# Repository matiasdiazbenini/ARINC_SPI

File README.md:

# ARINC_SPI

Repositorio de trabajo del proyecto PAMPA orientado a la recreacion logica/temporal de un enlace tipo ARINC 429 usando:

- 3 Raspberry Pi Pico / Pico 2 W
- 1 Raspberry Pi 3B+
- dashboard Flask
- bridge HTTP/SPI
- Prometheus + Grafana

Este repositorio estuvo originalmente centrado en el firmware del transmisor, pero fue ampliado y reorganizado para conservar en un solo lugar el estado real de la fase `arinc429_logic`, su documentacion y la evidencia de laboratorio.

## Estado actual

La fase validada hasta el momento es:

- `arinc429_logic`

Quedo validado:

- enlace `master -> slave` en `100 kbps` y `12.5 kbps`
- ACK reverso `slave -> master`
- captura pasiva con `ARINC-SNIFFER`
- exportacion por SPI hacia la Raspberry Pi 3B+
- bridge HTTP
- dashboard Flask
- Prometheus + Grafana
- corrida post tutor con `spi_errors = 0` en regimen estable
- separacion de errores SPI de arranque (`spi_startup_errors`) y operativos (`spi_errors`)
- transporte SPI por tramas completas validado con `sniffer_arinc429_logic_pio_frame`
- corrida PIO-frame de 6-7 horas con `spi_errors = 0`
- mecanismo DRDY implementado para consultar snapshot por demanda
- recuperacion V5 implementada para:
  - resincronizar captura ARINC esperando reposo electrico del canal
  - resetear transporte SPI `pio-frame` con trama completa de `32 bytes`
  - supervisar bridge/Flask con modo dios v2 (`arinc-supervisor.service`)
  - clasificar estados y ejecutar recuperacion escalonada
- paridad estricta implementada en RX y SNIFFER
- deteccion autonoma en sniffer de velocidad `FWD` entre `100 kbps` y `12.5 kbps`
- resync FWD separados entre arranque y regimen
- exportacion de pruebas a CSV, JSON y PDF desde la 3B+
- prueba de paridad estricta validada con balance exacto de contadores
- corridas finales de `8 horas` a `100 kbps` y `12.5 kbps`, ambas con cero
  errores operativos, cero errores de paridad, cero overflow y cero drops SPI
- validacion con osciloscopio de:
  - retorno a cero
  - pulsos de `5 us`
  - bit time de `10 us`
  - modo autorate:
    - `100 kbps`: palabra de `320 us` y gap visible de `44 us`
    - `12.5 kbps`: media celda de `40 us`, bit de `80 us` y gap visible de
      `360 us`
    - relacion de gaps `360/44 = 8.18`, coherente con la relacion teorica `8:1`
  - reconstruccion diferencial `+3.3 / 0 / -3.3 V`

## Estructura del repo

- [ARINC-TX](ARINC-TX/README.md)
  - firmware del nodo transmisor
- [ARINC-RX](ARINC-RX/README.md)
  - snapshot del firmware del nodo receptor usado en esta etapa
- [ARINC-SNIFFER](ARINC-SNIFFER/README.md)
  - snapshot del firmware sniffer y protocolo SPI asociado
- [HOST_3b+](HOST_3b+/README.md)
  - bridge SPI/HTTP, diagnosticos y scripts de host
- [DASHBOARD_WEB/arinc_dashboard](DASHBOARD_WEB/arinc_dashboard/README.md)
  - dashboard web operativo
- [prometheus](prometheus/README.md)
  - configuracion de Prometheus usada en la notebook
- [ELECTRICO](ELECTRICO/frontend_arinc429_lab/README.md)
  - front-end electrico de laboratorio, esquematico/PCB KiCad y relevamiento de componentes
- [imagenes](imagenes/)
  - capturas de osciloscopio organizadas por enlace y canal
- [docs](docs/README.md)
  - indice de documentacion y memoria externa del proyecto
- [tools](tools/)
  - scripts WSL para deploy, healthcheck y control de servicios en la 3B+
- [PROJECT_CONTEXT.md](PROJECT_CONTEXT.md)
  - archivo maestro de handoff para retomar rapido el trabajo
- raiz del repo:
  - README, contexto maestro y estado de fase
- `docs/`:
  - documentacion general
  - PDFs generados
  - fuentes Overleaf/LaTeX
  - scripts generadores
- `ELECTRICO/`:
  - proyecto KiCad inicial para el acondicionamiento electrico ARINC-like
  - PCB preliminar de laboratorio
  - relevamiento de componentes con precios, alternativas y correspondencia con el esquematico

## Topologia actual recomendada

- Pico transmisor:
  - genera `FWD_A` por `GP6` y `FWD_B` por `GP7`
- Pico receptor:
  - recibe `FWD`
  - responde `ACK` por `GP4/GP5`
- Pico sniffer:
  - escucha `FWD` y `REV`
  - no transmite sobre lineas ARINC
  - filtra por `label + SDI`
  - exporta snapshot/eventos por SPI
- Raspberry Pi 3B+:
  - consume SPI del sniffer
  - publica bridge HTTP local en `127.0.0.1:5100`
  - corre Flask hacia la red en `:5000`
- Notebook:
  - accede al dashboard
  - scrapea metricas desde Flask
  - corre Prometheus en `:9090`
  - corre Grafana en `:3000`

## Red recomendada

La configuracion que mejor resultado dio para estabilidad larga fue:

- notebook por Wi-Fi a Internet, si hace falta
- notebook por Ethernet directo a la Raspberry Pi 3B+
- IP fija de la notebook en Ethernet:
  - `192.168.50.1/24`
- IP fija de la Raspberry Pi 3B+ en Ethernet:
  - `192.168.50.2/24`

Se observo que esta configuracion es mas robusta que dejar la 3B+ colgada por Wi-Fi para el trafico operativo del sistema.

Acceso recomendado desde la notebook:

- dashboard Flask:
  - `http://192.168.50.2:5000`
- metricas para Prometheus:
  - `http://192.168.50.2:5000/metrics`

El bridge SPI/HTTP queda local dentro de la 3B+ en `http://127.0.0.1:5100`; Flask lo consulta por loopback.

## Modo stream post tutor

Ademas del modo laboratorio batch/ACK, quedo validada la transmision sin depender de bloques fijos de `1000` palabras:

- TX:
  - `arinc_tx_arinc429_logic_stream`
- RX:
  - `arinc_rx_arinc429_logic_stream`
- Sniffer:
  - `sniffer_arinc429_logic_pio_frame`

En este ensayo, `ARINC-TX` transmite rafagas de longitud variable y no espera ACK. `ARINC-RX` procesa palabras a medida que llegan y no emite ACK por `REV`. Por eso, en el dashboard, `TEMPERATURA`, `VELOCIDAD` y `ALTITUD` deben crecer; `ACK_BATCH` puede quedar ausente o congelado.

Criterios de prueba:

- `spi_errors = 0`
- `spi_drop_events = 0`
- `overflow_events = 0`
- `parity_errors_sniffer = 0`

Resultado de aproximadamente `10 horas`:

- `accepted_words = 22,756,775`
- `ack_events = 0`
- `spi_errors = 0`
- `spi_startup_errors = 6`
- `spi_drop_events = 0`
- `overflow_events = 0`
- `parity_errors_sniffer = 0`
- `fwd_resync_events = 3`

Evidencia:

- [evidencia_stream_aleatorio_post_tutor.md](docs/evidencia_stream_aleatorio_post_tutor.md)

## Modo autorate 100 kbps / 12.5 kbps

Para probar la capacidad de `ARINC-SNIFFER` de detectar la velocidad sin que TX
ni RX se la informen por configuracion externa, se agrego el target:

- TX:
  - `arinc_tx_arinc429_logic_stream_autorate`
  - `arinc_tx_arinc429_logic_stream_12k5` para forzar la velocidad baja en una
    prueba controlada

Este firmware elige al arrancar entre `100 kbps` y `12.5 kbps`. El RX stream
no requiere cambio porque su PIO recibe por flancos/nivel activo. El sniffer
publica la velocidad detectada como `detected_bit_rate_bps` y
`detected_bit_rate_txt` en `/stats`, y como `arinc_detected_bit_rate_bps` en
Prometheus.

Validacion observada:

- el TX arranco en distintas corridas tanto a `100 kbps` como a `12.5 kbps`
- corrida de `30 min` a `12.5 kbps`:
  - `detected_bit_rate_bps = 12500`
  - `received_words = 618,842`
  - `accepted_words = 185,652`
  - `spi_errors = 0`
- corrida de `30 min` a `100 kbps`:
  - `detected_bit_rate_bps = 100000`
  - `received_words = 4,807,727`
  - `accepted_words = 1,442,318`
  - `spi_errors = 0`
- ambas corridas cerraron con:
  - `parity_errors_sniffer = 0`
  - `overflow_events = 0`
  - `spi_drop_events = 0`
  - balance de clasificacion igual a `0`
- corridas finales de `8 horas`:
  - `12.5 kbps`: `received_words = 9,876,638`,
    `accepted_words = 2,962,992`, `spi_errors = 0`
  - `100 kbps`: `received_words = 76,707,606`,
    `accepted_words = 23,012,283`, `spi_errors = 0`
  - ambas con `parity_errors_sniffer = 0`, `overflow_events = 0`,
    `spi_drop_events = 0`, `fwd_operational_resync_events = 0` y
    `supervisor_health = ok`

Evidencia:

- [evidencia_autorate_100k_12k5.md](docs/evidencia_autorate_100k_12k5.md)
- [evidencia_corridas_finales_autorate_8h.md](docs/evidencia_corridas_finales_autorate_8h.md)

## Forma recomendada de trabajo

Hay dos maneras comodas de trabajar:

- abrir la raiz del repo para tener toda la arquitectura visible
- abrir una subcarpeta puntual cuando quieras concentrarte en un componente

Por ejemplo:

- `ARINC-TX/`
- `ARINC-RX/`
- `ARINC-SNIFFER/`
- `HOST_3b+/`
- `DASHBOARD_WEB/arinc_dashboard/`

Tambien se pueden abrir varias ventanas de VS Code en paralelo, una por componente, sin problema.

## Operacion Raspberry 3B+ desde WSL

Ademas de WinSCP, el repo incluye scripts para actualizar y verificar la 3B+
por SSH/rsync desde WSL:

- [Operacion Raspberry Pi 3B+ con scripts](docs/operacion_raspberry_3b_deploy.md)

Comandos principales:

```bash
./tools/raspi_deploy.sh
./tools/raspi_healthcheck.sh
./tools/raspi_services.sh status
```

## Perfil operativo recomendado

Para el bridge/dashboard, el perfil que mejor balance dio entre fluidez y estabilidad fue:

- modo PIO-frame validado post tutor:
  - `ARINC_SPI_TRANSFER_MODE = pio-frame`
  - `ARINC_SPI_MANUAL_CS = 1`
  - `ARINC_SPI_CS_SETUP_US = 100`
  - `ARINC_SPI_CS_HOLD_US = 100`
  - `ARINC_SPI_HZ = 8000000`
  - `ARINC_SPI_BYTE_DELAY_US = 0`
  - corrida de aproximadamente `9 horas` con `spi_errors = 0`
- fallback PIO-frame conservador:
  - `ARINC_SPI_HZ = 400000`
- modo byte validado como fallback estable:
  - `ARINC_SPI_TRANSFER_MODE = byte`
  - `ARINC_SPI_HZ = 800000`
  - `ARINC_SPI_BYTE_DELAY_US = 25`

Perfil historico estable previo al PIO-frame:

- `ARINC_SPI_HZ = 800000`
- `ARINC_SPI_TRANSFER_MODE = byte`
- `ARINC_SPI_BYTE_DELAY_US = 25`
- `ARINC_SPI_POLL_SEC = 0.006`
- `ARINC_SPI_STATS_SEC = 0.06`
- `ARINC_SPI_RESPONSE_DELAY_SEC = 0.00005`
- refresh Flask:
  - `33 ms`

El perfil de estres mas agresivo fue probado y aguanto varias horas, pero con una tasa de `spi_errors` mucho mayor, por lo que no se deja como modo continuo recomendado.

## Documentos clave

- [Entrega consolidada para el tutor](docs/entrega_tutor/README.md)
- [Trabajo final en formato tesis PDF](docs/pdf/trabajo_final_arinc429.pdf)
- [Fuente LaTeX del trabajo final](docs/tex/trabajo_final_arinc429.tex)
- [PROJECT_CONTEXT.md](PROJECT_CONTEXT.md)
- [FASE2_ARINC429_LOGIC.md](FASE2_ARINC429_LOGIC.md)
- [resumen_proyecto_arinc429.md](docs/resumen_proyecto_arinc429.md)
- [instructivo_osciloscopio_arinc429_logic.md](docs/instructivo_osciloscopio_arinc429_logic.md)
- [evidencia_spi_errors_cero_post_tutor.md](docs/evidencia_spi_errors_cero_post_tutor.md)
- [evidencia_spi_pio_frame_post_tutor.md](docs/evidencia_spi_pio_frame_post_tutor.md)
- [procedimiento_prueba_paridad_estricta.md](docs/procedimiento_prueba_paridad_estricta.md)
- [procedimiento_registro_estadistico.md](docs/procedimiento_registro_estadistico.md)
- [evidencia_corrida_final_stream_8mhz_8h.md](docs/evidencia_corrida_final_stream_8mhz_8h.md)
- [evidencia_corridas_finales_autorate_8h.md](docs/evidencia_corridas_finales_autorate_8h.md)
- [evidencia_osciloscopio_autorate_20260629.md](docs/evidencia_osciloscopio_autorate_20260629.md)
- [tesis_fuente_overleaf_arinc429.tex](docs/tex/tesis_fuente_overleaf_arinc429.tex)
- [trabajo_final_arinc429.tex](docs/tex/trabajo_final_arinc429.tex)
- [modelo_osi_arquitectura_arinc429.tex](docs/tex/modelo_osi_arquitectura_arinc429.tex)
- [osciloscopio_descripcion_imagenes.tex](docs/tex/osciloscopio_descripcion_imagenes.tex)

## Nota sobre ramas

Por pedido explicito del usuario, no deben tocarse las ramas:

- `MIL-M`
- `MIL-E`
- `FLASK-MIL`
- `version_estable`

correspondientes a trabajo ajeno al desarrollo ARINC actual.

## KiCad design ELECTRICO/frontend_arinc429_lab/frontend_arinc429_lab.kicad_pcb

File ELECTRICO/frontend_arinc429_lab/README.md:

# Front-end electrico ARINC 429 - banco

Proyecto KiCad inicial para revisar el acondicionamiento electrico de laboratorio.

## Estado vigente

La configuracion de banco vigente usa TL062 y fue validada el 20 de agosto de
2026 a `12,5 kbps` y `100 kbps`. El TX recibe `FWD_A` por `GP6` y `FWD_B` por
`GP7`. El detalle se encuentra en
[avance_frontend_electrico_20260820.md](../../docs/avance_frontend_electrico_20260820.md)
y las capturas originales en [evidencia/20-08](evidencia/20-08/README.md).

## Archivos

- `frontend_arinc429_lab.kicad_pro`: proyecto KiCad.
- `frontend_arinc429_lab.kicad_sch`: esquematico funcional.
- `frontend_arinc429_lab.kicad_pcb`: PCB preliminar de laboratorio.
- `exports/frontend_arinc429_lab.svg`: export del esquematico.
- `exports/frontend_arinc429_lab_pcb.svg`: vista rapida de distribucion PCB.
- `relevamiento_componentes_frontend_electrico.md`: componentes, precios, equivalencias y busqueda de disponibilidad.
- `frontend_arinc429_tl082_rework.md`: revision nueva usando TL082CP como base de TX/RX analogico.
- `exports/frontend_arinc429_tl082_rework.svg`: esquematico funcional de la revision TL082CP.
- `frontend_arinc429_tl082_circuit.kicad_pro`: proyecto KiCad del circuito TL082CP completo.
- `frontend_arinc429_tl082_circuit.kicad_sch`: esquematico de circuito con resistencias, capacitores, conectores, TL082CP y adaptacion logica.
- `exports/frontend_arinc429_tl082_circuit.svg`: export del esquematico de circuito.
- `exports/frontend_arinc429_tl082_circuit.pdf`: export PDF del esquematico de circuito.
- `memoria_calculo_frontend_tl082.tex`: memoria de calculo editable en LaTeX.
- `exports/memoria_calculo_frontend_tl082.pdf`: memoria de calculo compilada.
- `proteus/frontend_arinc429_proteus.pdsprj`: simulacion Proteus 8.15 del
  front-end TX/RX con TL082 y comparadores LM393.
- `evidencia/20260814_banco_tl082/README.md`: resultado y capturas de la
  validacion fisica del prototipo a `12,5 kbps` y `100 kbps`.
- `evidencia/20-08/README.md`: validacion vigente con TL062 a `12,5 kbps` y
  `100 kbps`.

## Alcance

Este esquema y la PCB son una base de revision y prototipo. No son todavia una
PCB final ni un transceptor certificable para campo.

## Conexion funcional

- `GP6`: TX_A_LOGIC / FWD_A.
- `GP7`: TX_B_LOGIC / FWD_B.
- `GP4`: RX_A_LOGIC.
- `GP5`: RX_B_LOGIC.
- `LINE_A/LINE_B`: par diferencial de banco.
- `+6V/-6V`: alimentacion del driver bipolar.
- `+3V3`: logica Pico y salidas de comparadores.
- `GND`: referencia comun del banco.

## Conexiones explicitas del esquematico

| Net | Desde | Hasta | Funcion |
| --- | --- | --- | --- |
| `TX_A_LOGIC` | Pico `GP6` | entrada `U1A` | dato logico lado A antes de acondicionar |
| `TX_B_LOGIC` | Pico `GP7` | entrada `U1A` | dato logico lado B antes de acondicionar |
| `LINE_A` | salida `U1A` | `J2 pin 1` y entrada `A_SENSE` | conductor A bipolar |
| `LINE_B` | salida `U1B` | `J2 pin 2` y entrada `B_SENSE` | conductor B bipolar |
| `GND_REF` | `J2 pin 3` | `GND_COMUN` | referencia de banco para medicion |
| `A_SENSE` | divisor/proteccion de `LINE_A` | entrada de `U2A` | senal reducida para comparar |
| `B_SENSE` | divisor/proteccion de `LINE_B` | entrada de `U2B` | senal reducida para comparar |
| `VTH_COMP` | divisor `R11/R12` | entradas de referencia de `U2A/U2B` | umbral de decision RX |
| `RX_A_LOGIC` | salida `U2A` | Pico `GP4` | senal recuperada A, ya en 0..3,3 V |
| `RX_B_LOGIC` | salida `U2B` | Pico `GP5` | senal recuperada B, ya en 0..3,3 V |
| `+3V3_LOGIC` | Pico/fuente 3,3 V | U2, pull-ups, divisor de umbral | alimentacion logica |
| `+6V_TX` | fuente bipolar | `U1 V+` | alimentacion positiva del TX analogico |
| `-6V_TX` | fuente bipolar | `U1 V-` | alimentacion negativa del TX analogico |
| `GND_COMUN` | Pico/fuente | J2, RX, divisor de umbral | referencia comun |

## Convencion visual

| Tipo de linea | Convencion |
| --- | --- |
| Senales y linea A/B | verde, trazo continuo |
| Alimentacion | rojo, trazo continuo mas grueso |
| GND y referencias | azul, trazo punteado |
| Umbral `VTH_COMP` | violeta, trazo punteado fino |
| Retorno RX hacia Pico | naranja, trazo punto-raya |

`VTH_COMP` no va a `J2`. `J2` solo expone la linea de banco `LINE_A`,
`LINE_B` y `GND_REF`. El umbral `VTH_COMP` es interno del receptor RX y entra a
los comparadores `U2A/U2B`.

`R11` y `R12` estan conectadas en serie como divisor resistivo:

```text
+3V3_LOGIC -> R11 -> VTH_COMP -> R12 -> GND_COMUN
```

La linea violeta entre `R11` y `R12` es el nodo medio del divisor. Las lineas
violetas que aparecen en `U2A` y `U2B` son esa misma red `VTH_COMP`; representan
la referencia de comparacion, no una conexion hacia la linea ARINC.

Las alimentaciones y referencias se muestran como etiquetas de red locales para
evitar cruces innecesarios. En KiCad, dos puntos con la misma etiqueta pertenecen
a la misma conexion electrica aunque no exista un cable dibujado entre ambos.

## Revision de conexiones criticas

- `U2A VDD` queda en `+3V3_LOGIC`.
- `U2A VSS` queda en `GND_COMUN`.
- `U2B VDD` queda en `+3V3_LOGIC`.
- `U2B VSS` queda en `GND_COMUN`.
- `J2 pin 3 GND_REF` queda unido a `GND_COMUN`.
- Los divisores `A_SENSE` y `B_SENSE` cierran por `GND_COMUN`.
- El divisor `R11/R12` genera `VTH_COMP` desde `+3V3_LOGIC` hacia `GND_COMUN`.
- `VTH_COMP` entra como referencia a `U2A/U2B`; no sale al conector de linea.
- `RX_A_LOGIC` vuelve a `GP4` y `RX_B_LOGIC` vuelve a `GP5`.
- `U1` usa alimentacion bipolar separada: `+6V_TX` y `-6V_TX`.

## PCB preliminar

La PCB preliminar se genero para tener una aproximacion editable en KiCad antes
de cerrar la compra final de componentes. La revision vigente es `Rev B`: deja
los footprints separados por bloque funcional y no incluye ruteo final. KiCad
debe mostrar las conexiones pendientes como airwires/ratsnest para que el ruteo
se haga manualmente cuando ya esten definidos los encapsulados reales.

La version compacta anterior, con pistas preliminares cruzando la placa, no se
considera valida como layout para mostrar ni fabricar. La distribucion vigente
esta pensada para banco:

- conectores de entrada/salida en bordes;
- `J1` como header simple hacia la Pico de prueba;
- `J2` como bornera de linea `LINE_A`, `LINE_B`, `GND_REF`;
- `J3` como bornera de alimentacion `+3V3`, `+6V`, `-6V`, `GND`;
- `U1` en DIP8 para TL062 o equivalente de op-amp dual;
- `U2` en DIP8 para LM393N de banco o adaptador hacia MCP6562/LMV393 si luego se compran SMD;
- resistencias y capacitores THT para facilitar cambios;
- testpoints para `LINE_A`, `LINE_B`, `GND_COMUN` y `VTH_COMP`;
- pull-ups `R13/R14` marcados como `4k7/DNP`: se montan si se usa LM393/LM393B y se dejan sin montar si el comparador final tiene salida push-pull.

La PCB no debe enviarse a fabricar sin revision manual en KiCad. Falta confirmar
footprints exactos, dimensiones reales de borneras, corriente disponible de las
fuentes, separaciones, DRC y comportamiento analogico con componentes reales.

## Revision TL082CP

La revision [frontend_arinc429_tl082_rework.md](frontend_arinc429_tl082_rework.md)
documenta el rediseño pedido con TL082CP:

- TX bipolar con dos amplificadores diferenciales retroalimentados;
- `Zout` diferencial aproximada de `78 ohm` usando `39 ohm` por rama;
- J2 como linea ARINC-like de banco;
- RX analogico con TL082CP y alta impedancia;
- restriccion explicita: el RX TL082-only no debe conectarse directo a GPIO sin
  una etapa final de decision/proteccion.

El esquematico de circuito [frontend_arinc429_tl082_circuit.kicad_sch](frontend_arinc429_tl082_circuit.kicad_sch)
complementa esa revision con una implementacion electrica concreta:

- `U1A/U1B TL082CP`: convierten `TX_A_LOGIC/TX_B_LOGIC` en `LINE_A/LINE_B`
  de aproximadamente `+5/0/-5 V` por conductor, con redes
  `22 kohm / 33 kohm` y ganancia `1,5`.
- `R9/R10 = 39 ohm`: aproximan `Zout` diferencial a `78 ohm`.
- `U2A/U2B TL082CP`: leen `LINE_A/LINE_B` con alta impedancia y generan
  senales analogicas con `99 kohm / 10 kohm`, ganancia `10/99` y
  `Zin` diferencial aproximada de `99 kohm`.
- `U3 MCP6562`: convierte las senales analogicas a `RX_A_LOGIC/RX_B_LOGIC`
  seguros y activos en alto para `GP4/GP5`; la senal sesgada entra por la
  entrada no inversora y `VTH_RX` por la inversora.
- `R21/R22 = 1 kohm / 1 kohm`: generan `VREF_RX = 1,635 V` al incluir
  la carga real.
- `R23 || R25 = 6,7 kohm || 38 kohm` y `R24 = 10 kohm`: generan
  `VTH_RX = 2,102 V`.
- Con resistencias independientes de `1 %`, el peor caso conserva unos
  `176,6 mV` contra falso activo y `144,2 mV` para el activo minimo. Con `5 %`,
  el segundo margen puede hacerse negativo, por lo que hay que medir y aparear.
- `C1..C11`: desacople y filtrado local de referencias.

Aunque se prioriza TL082CP, el esquematico incluye `U3` porque la salida de un
TL082 alimentado en bipolar no debe entrar directamente a una Raspberry Pi Pico.
Sin esa etapa, el circuito no queda cerrado de forma segura.

La [memoria de calculo](exports/memoria_calculo_frontend_tl082.pdf) justifica
ganancias, impedancias, referencias, tolerancias, desacople y respuesta temporal
para `100 kbit/s` y `12,5 kbit/s`. La revision E ya incorpora el recalculo de
`VREF_RX` y `VTH_RX` con los valores adquiridos.

## Estado de componentes para la revision E

Ya disponibles: dos TL082CP, resistencias de `22 kohm`, `33 kohm`, `99 kohm`,
`10 kohm`, `1 kohm`, `6,7 kohm` y `38 kohm`, siete capacitores codigo `104`
de `100 nF`, cuatro capacitores de `10 uF`, bornera y cableado.

Pendientes o por confirmar:

- un `MCP6562-E/P`;
- dos resistencias de `39 ohm` para R9/R10;
- fuente bipolar regulada `+12 V / GND / -12 V`;
- confirmar tres zocalos PDIP-8 y definir la placa de montaje.

Las resistencias de `38 kohm` se usan como R25 en paralelo con R23 para ajustar
el umbral; no reemplazan las resistencias de salida de `39 ohm`.

## Checkpoint de validacion en banco

La evidencia del 20 de agosto de 2026 confirma el funcionamiento correcto del
front-end con TL062 a `12,5 kbps` y `100 kbps`. Se verificaron la salida
diferencial, los tiempos de bit, el retorno a cero y la recuperacion logica. El
detalle y las capturas originales se conservan en
[evidencia/20-08](evidencia/20-08/README.md).

### Antecedente de la revision anterior

La evidencia del 14 de agosto de 2026 confirma el funcionamiento de la cadena
completa a `12,5 kbps`, desde la Pico TX y el front-end electrico hasta la
recuperacion logica, el sniffer y la visualizacion. En la corrida observada no
se registraron errores.

El mismo montaje no resulto confiable a `100 kbps`: los TL082CP ensayados
presentaron rampas de aproximadamente `8..12 us`, un tiempo comparable con el
periodo de bit de `10 us`. A `12,5 kbps`, cuyo periodo es `80 us`, queda una
meseta util suficiente. El detalle y las capturas originales se conservan en
[evidencia/20260814_banco_tl082](evidencia/20260814_banco_tl082/README.md).

## Validacion minima

1. Medir `LINE_A` y `LINE_B` contra GND.
2. Medir `MATH = LINE_A - LINE_B`.
3. Confirmar aproximadamente `+10 V`, `0 V`, `-10 V` diferencial.
4. Confirmar que `RX_A_LOGIC` y `RX_B_LOGIC` nunca excedan `0..3,3 V`.

## Explicacion tecnica

El esquema representa un acondicionador electrico entre la logica de una
Raspberry Pi Pico y una linea diferencial tipo ARINC 429 de laboratorio.

La Pico entrega dos senales logicas: `TX_A_LOGIC` por `GP6` y `TX_B_LOGIC` por
`GP7`. Esas senales entran al bloque `TX bipolar`. La primera etapa, `U1A`,
esta planteada como un amplificador diferencial con ganancia 1,5:

```text
LINE_A = 1,5 * (TX_A_LOGIC - TX_B_LOGIC)
```

La segunda etapa, `U1B`, invierte `LINE_A`:

```text
LINE_B = -LINE_A
```

De esa manera, cuando `GP6` esta alto y `GP7` bajo, la linea queda
aproximadamente `LINE_A=+5 V` y `LINE_B=-5 V`. Cuando se invierten los GPIO, la
polaridad diferencial tambien se invierte. Cuando ambos GPIO estan en cero, el
resultado esperado es `LINE_A=0 V` y `LINE_B=0 V`.

El conector `J2` expone el par `LINE_A/LINE_B`. En ese punto se debe medir con
osciloscopio tanto cada linea contra masa como la resta `MATH = LINE_A - LINE_B`.
El diferencial esperado es `+10 V`, `0 V` y `-10 V`.

El bloque `RX protegido y comparadores` toma `LINE_A` y `LINE_B` y no las lleva
directamente a la Pico. Primero cada linea pasa por un divisor/proteccion
(`A_SENSE` y `B_SENSE`). Luego `U2A` y `U2B` comparan esos nodos contra
`VTH_COMP`, aproximadamente `1,50 V`.

Las salidas de los comparadores vuelven a la Pico como senales logicas seguras:

```text
U2A -> RX_A_LOGIC -> GP4
U2B -> RX_B_LOGIC -> GP5
```

Esas salidas deben estar siempre entre `0 V` y `3,3 V`. Si el comparador elegido
es `LM393/LM393B`, la salida es open collector y necesita pull-up a `3V3`, no a
`5V`, para no danar la Pico.

## Explicacion simple

La Pico sola no puede sacar una senal ARINC real porque sus pines solo manejan
`0 V` y `3,3 V`. Entonces el circuito hace de traductor.

Primero la Pico dice que quiere transmitir usando dos pines:

- `GP6` representa el lado A.
- `GP7` representa el lado B.

Despues el bloque TX agranda esa senal y la convierte en una senal bipolar:

- si A esta activo, el cable A queda en `+5 V` y el cable B en `-5 V`;
- si B esta activo, el cable A queda en `-5 V` y el cable B en `+5 V`;
- si no hay pulso, ambos cables quedan cerca de `0 V`.

Eso es lo que se quiere ver en el osciloscopio como ARINC de laboratorio.

Luego viene el bloque RX. Ese bloque hace el trabajo inverso: mira cual de los
dos cables esta positivo, baja la senal a un valor seguro y la vuelve a entregar
a la Pico como `0 V` o `3,3 V`.

En criollo: el TX convierte la senal chica de la Pico en una senal grande tipo
ARINC, y el RX convierte esa senal grande otra vez en una senal chica que la Pico
puede leer sin quemarse.

La parte importante que debe quedar clara es esta:

```text
Linea ARINC-like -> RX -> comparadores -> RX_A_LOGIC/RX_B_LOGIC -> GP4/GP5
```

Ese es el regreso hacia la Pico.

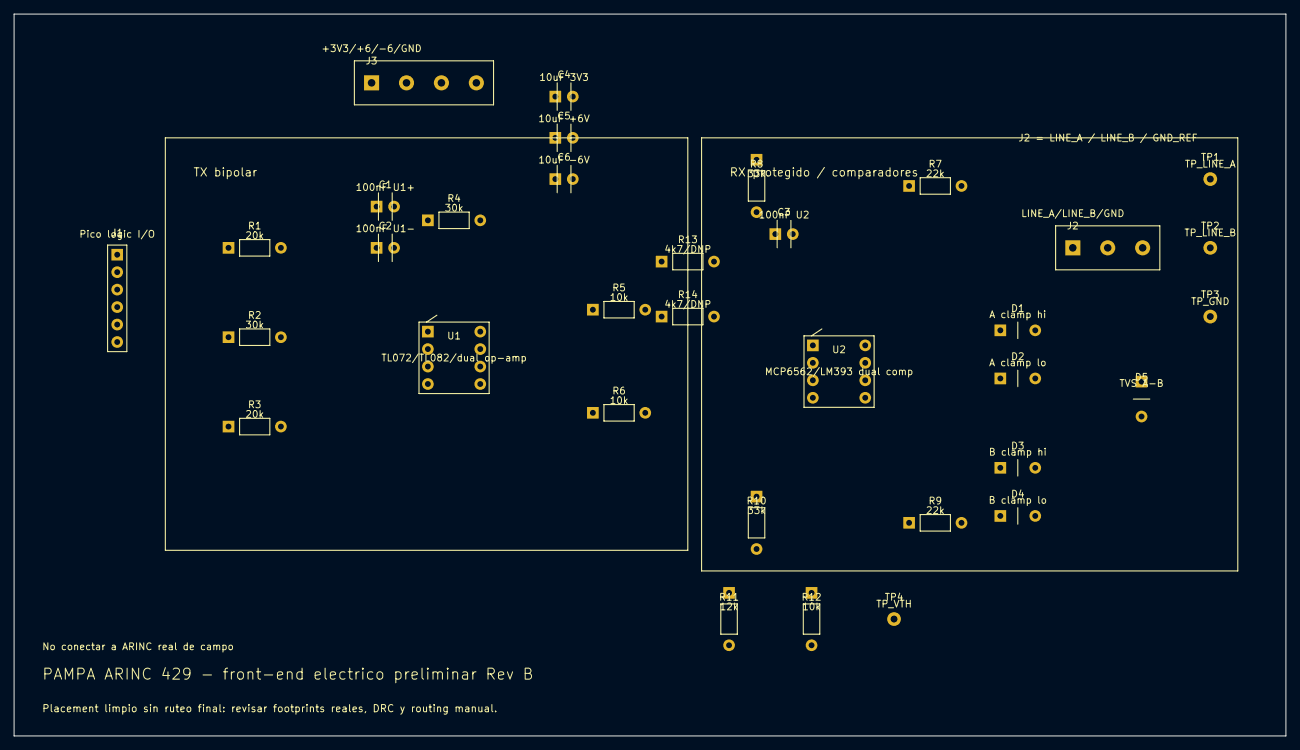
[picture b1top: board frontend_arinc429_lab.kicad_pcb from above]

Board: 2 copper layers, 185.0 x 105.0 mm, 34 parts (0 on the bottom side), 16 nets, no tracks yet.

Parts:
C1: 100nF U1+; C_Disc_D3.0mm_W1.6mm_P2.50mm
C2: 100nF U1-; C_Disc_D3.0mm_W1.6mm_P2.50mm
C3: 100nF U2; C_Disc_D3.0mm_W1.6mm_P2.50mm
C4: 10uF 3V3; C_Disc_D3.0mm_W1.6mm_P2.50mm
C5: 10uF +6V; C_Disc_D3.0mm_W1.6mm_P2.50mm
C6: 10uF -6V; C_Disc_D3.0mm_W1.6mm_P2.50mm
D1: A clamp hi; D_DO-35_SOD27_P7.62mm_Horizontal
D2: A clamp lo; D_DO-35_SOD27_P7.62mm_Horizontal
D3: B clamp hi; D_DO-35_SOD27_P7.62mm_Horizontal
D4: B clamp lo; D_DO-35_SOD27_P7.62mm_Horizontal
D5: TVS A-B; D_DO-35_SOD27_P7.62mm_Horizontal
J1: Pico logic I/O; PinHeader_1x06_P2.54mm_Vertical
J2: LINE_A/LINE_B/GND; TerminalBlock_1x03_P5.08mm
J3: +3V3/+6/-6/GND; TerminalBlock_1x04_P5.08mm
R1, R3: 20k; R_Axial_DIN0207_L6.3mm_D2.5mm_P7.62mm_Horizontal
R2, R4: 30k; R_Axial_DIN0207_L6.3mm_D2.5mm_P7.62mm_Horizontal
R5, R6, R12: 10k; R_Axial_DIN0207_L6.3mm_D2.5mm_P7.62mm_Horizontal
R7, R9: 22k; R_Axial_DIN0207_L6.3mm_D2.5mm_P7.62mm_Horizontal
R8, R10: 33k; R_Axial_DIN0207_L6.3mm_D2.5mm_P7.62mm_Horizontal
R11: 12k; R_Axial_DIN0207_L6.3mm_D2.5mm_P7.62mm_Horizontal
R13, R14: 4k7/DNP; R_Axial_DIN0207_L6.3mm_D2.5mm_P7.62mm_Horizontal
TP1: TP_LINE_A; TestPoint_THTPad_D2.0mm_Drill1.0mm
TP2: TP_LINE_B; TestPoint_THTPad_D2.0mm_Drill1.0mm
TP3: TP_GND; TestPoint_THTPad_D2.0mm_Drill1.0mm
TP4: TP_VTH; TestPoint_THTPad_D2.0mm_Drill1.0mm
U1: TL072/TL082/dual op-amp; DIP-8_W7.62mm
U2: MCP6562/LM393 dual comp; DIP-8_W7.62mm

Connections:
+3V3_LOGIC: C3.1, C4.1, D1.2, D3.2, J1.5, J3.1, R11.1, R13.1, R14.1, U2.8
+6V_TX: C1.1, C5.1, J3.2, U1.8
-6V_TX: C2.1, C6.1, J3.3, U1.4
A_SENSE: D1.1, D2.2, R7.2, R8.1, U2.3
B_SENSE: D3.1, D4.2, R9.2, R10.1, U2.5
GND_COMUN: C1.2, C2.2, C3.2, C4.2, C5.2, C6.2, D2.1, D4.1, J1.6, J2.3, J3.4, R2.2, R8.2, R10.2, R12.2, TP3.1, U1.5, U2.4
LINE_A: D5.1, J2.1, R4.1, R5.1, R7.1, TP1.1, U1.1
LINE_B: D5.2, J2.2, R6.1, R9.1, TP2.1, U1.7
RX_A_LOGIC: J1.3, R13.2, U2.1
RX_B_LOGIC: J1.4, R14.2, U2.7
TX_A_LOGIC: J1.1, R1.1
TX_B_LOGIC: J1.2, R3.1
U1A_NEG: R3.2, R4.2, U1.2
U1A_POS: R1.2, R2.1, U1.3
U1B_NEG: R5.2, R6.2, U1.6
VTH_COMP: R11.2, R12.1, TP4.1, U2.2, U2.6

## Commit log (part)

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2026-04-16 Intento de arreglo
2026-04-16 Arreglando
2026-04-16 Casi cagada
2026-04-17 cambios
2026-04-17 Version sin cagadas
2026-04-17 Versión estable?
2026-04-17 Estable?
2026-04-17 NO LO ROMPAS
2026-04-17 Estableee
2026-04-17 push yo
2026-04-17 push mati yo
2026-04-17 Gap 200u
2026-04-17 Gap 5ku
2026-04-18 volvi al anterior
2026-04-18 Subo a 7k
2026-04-18 Subo a 200
2026-04-18 Bajo a 100
2026-04-18 Bajo a 200
2026-04-21 agregado todo lo de la Raspi
2026-04-22 Grafana funcionando
2026-04-24 GP2/GP3 M-S; GP4/GP5 S-M; 2 enlaces simplex + Flask + Grafana
2026-04-24 Cambio en el log
2026-04-24 Data gap 5k
2026-04-24 Data gap 7k
2026-04-24 Pruebas
2026-04-24 Cambio en bus.c
2026-04-24 Cambio en bus.c 2
2026-04-24 Cambio en main.c
2026-04-24 Volvi al main anterior
2026-04-24 No se que hice
2026-04-25 Borre cosas
2026-04-25 Vuelta a 0
2026-04-25 Mando bits
2026-04-25 Mando bytes
2026-04-25 Mando bytes arreglando
2026-04-25 Mando bytes sync arreglada
2026-04-25 Prueba mejorada
2026-04-25 Prueba mejorada 16
2026-04-25 Prueba mejorada mas piola
2026-04-25 Manchester
2026-04-25 Manchester con bus
2026-04-25 Manchester con bus with paridad
2026-04-25 Palabras de MIL
2026-04-25 Mejora
2026-04-25 Half-duplex
2026-04-25 Sniffer
2026-04-25 Snifer
2026-04-25 Cambios de TR
2026-04-25 Cambios de TR funciona
2026-04-25 Cambios en bus
2026-04-25 Agrego sync por tipo y sniffer secuencial
2026-04-25 Subo velocidad
2026-04-25 Cambio de ms a us
2026-04-25 Mejora de la logica
2026-04-26 Estable
2026-04-26 CODEMODE
2026-04-26 Manejo de errores del BC
2026-04-26 Intento de PIO
2026-04-27 Intento de PIO main con el protocolo
2026-04-27 Intento de PIO main con el protocolo/Cambio es bus
2026-04-27 Prueba aislada
2026-04-27 PIO RX
2026-05-04 Estable palabra F0
2026-05-04 SYNC + CMD + DATA[0] + DATA[1] + DATA[2]
2026-05-04 SYNC + CMD + DATA[0]
2026-05-05 FUNCIONA HASTA ACA
2026-05-05 PAcketes bien
2026-05-05 Nuevo patron, checksum
2026-05-05 Mejora en cmd
2026-05-05 Palabra automatico
2026-05-05 Yendo al mil
2026-05-05 Intento de halfduplex
2026-05-05 Halfduplex logrado, falta mejorar
2026-05-05 TR 1
2026-05-07 agregado lo de la raspi 3b+
2026-05-08 Implement 1553-like BC/RT transactions for TR=0 and TR=1
2026-05-08 Add parity-word support for TR0 and TR1 1553-like transactions
2026-05-09 Add parity-word transactions and RT error handling
2026-05-09 Add high-level BC and RT transaction APIs
2026-05-09 Flask
2026-05-09 TR 0 Estable
2026-05-09 Limpio
2026-05-10 BC/RT limpio + BIT_PERIOD_US=500 + retransmisión BC_TO_RT estable
2026-05-11 Version estable optimizada
2026-05-22 funcional master-slave+sniffer->3b+>Flask
2026-05-23 comunicacion robusta lograda
2026-05-24 limite fisico encontrado: word gap en 3
2026-05-24 testeos de capacidad
2026-05-26 sistema 100% funcional. fase 1 terminada
2026-06-02 consolida fase arinc429 logic con host docs y evidencia
2026-06-02 reorganiza repo completo y separa master en subcarpeta
2026-06-03 renombra componentes a nombres funcionales
2026-06-03 ultimos cambios despues de la unificacion
2026-06-03 Organize ARINC project root
2026-06-12 Cierra fase logica ARINC 429
2026-06-19 docs: add 3b service command reference
2026-06-24 docs: consolidate arinc validation evidence
2026-06-24 feat: use drdy driven sniffer bridge
2026-06-24 chore: expose drdy request counters
2026-06-24 feat: add ARINC autorate detection
2026-06-25 feat: add ARINC recovery supervisor
2026-06-25 style: simplify ARINC dashboard
2026-06-25 docs: record autorate final validation
2026-06-25 docs: add final ARINC thesis draft
2026-06-29 docs: add final oscilloscope autorate evidence
